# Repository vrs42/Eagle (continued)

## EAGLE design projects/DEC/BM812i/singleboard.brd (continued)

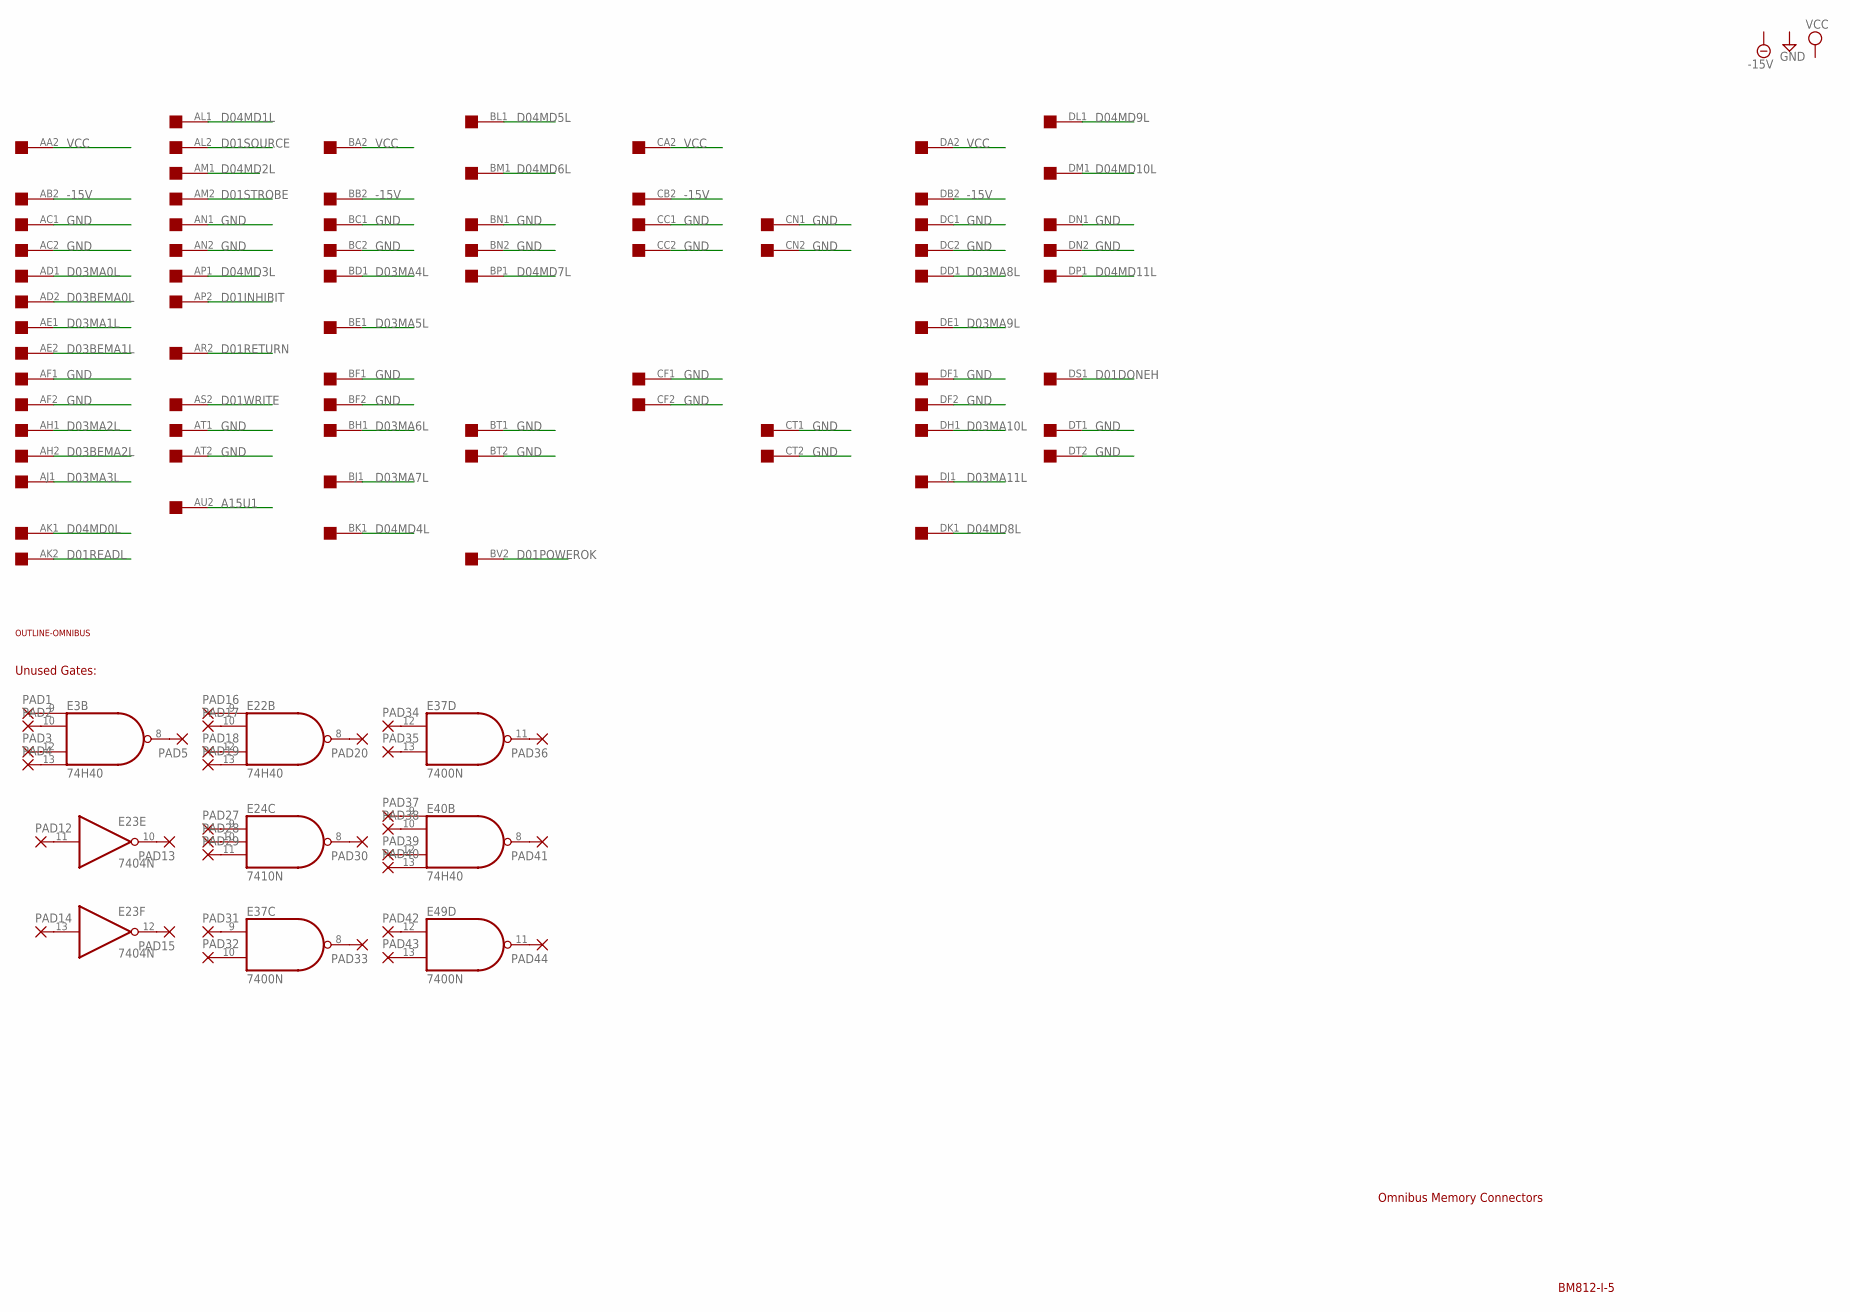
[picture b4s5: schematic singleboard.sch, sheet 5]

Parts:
E3, E22, E40: 74H40; DIL14
E23: 7404N; DIL14
E24: 7410N; DIL14
E37, E49: 7400N; DIL14
PAD1, PAD2, PAD3, PAD4, PAD5, PAD12, PAD13, PAD14, PAD15, PAD16, PAD17, PAD18, PAD19, PAD20, PAD27, PAD28, PAD29, PAD30, PAD31, PAD32, PAD33, PAD34, PAD35, PAD36, PAD37, PAD38, PAD39, PAD40, PAD41, PAD42, PAD43, PAD44: 1,6/0,8
U$1: QUAD; EDGE-CON8
U$2: OUTLINE-OMNIBUS; OMNIBUS

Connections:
-15V: U$1.AB2, U$1.BB2, U$1.CB2, U$1.DB2
A15U1: U$1.AU2; also elsewhere on the board
D01DONEH: U$1.DS1; also elsewhere on the board
D01INHIBIT: U$1.AP2; also elsewhere on the board
D01POWEROK: U$1.BV2; also elsewhere on the board
D01READL: U$1.AK2; also elsewhere on the board
D01RETURN: U$1.AR2; also elsewhere on the board
D01SOURCE: U$1.AL2; also elsewhere on the board
D01STROBE: U$1.AM2; also elsewhere on the board
D01WRITE: U$1.AS2; also elsewhere on the board
D03BEMA0L: U$1.AD2; also elsewhere on the board
D03BEMA1L: U$1.AE2; also elsewhere on the board
D03BEMA2L: U$1.AH2; also elsewhere on the board
D03MA0L: U$1.AD1; also elsewhere on the board
D03MA1L: U$1.AE1; also elsewhere on the board
D03MA2L: U$1.AH1; also elsewhere on the board
D03MA3L: U$1.AJ1; also elsewhere on the board
D03MA4L: U$1.BD1; also elsewhere on the board
D03MA5L: U$1.BE1; also elsewhere on the board
D03MA6L: U$1.BH1; also elsewhere on the board
D03MA7L: U$1.BJ1; also elsewhere on the board
D03MA8L: U$1.DD1; also elsewhere on the board
D03MA9L: U$1.DE1; also elsewhere on the board
D03MA10L: U$1.DH1; also elsewhere on the board
D03MA11L: U$1.DJ1; also elsewhere on the board
D04MD0L: U$1.AK1; also elsewhere on the board
D04MD1L: U$1.AL1; also elsewhere on the board
D04MD2L: U$1.AM1; also elsewhere on the board
D04MD3L: U$1.AP1; also elsewhere on the board
D04MD4L: U$1.BK1; also elsewhere on the board
D04MD5L: U$1.BL1; also elsewhere on the board
D04MD6L: U$1.BM1; also elsewhere on the board
D04MD7L: U$1.BP1; also elsewhere on the board
D04MD8L: U$1.DK1; also elsewhere on the board
D04MD9L: U$1.DL1; also elsewhere on the board
D04MD10L: U$1.DM1; also elsewhere on the board
D04MD11L: U$1.DP1; also elsewhere on the board
GND: E3.7 (GND), E22.7 (GND), E23.7 (GND), E24.7 (GND), E37.7 (GND), E40.7 (GND), E49.7 (GND), U$1.AC1, U$1.AC2, U$1.AF1, U$1.AF2, U$1.AN1, U$1.AN2, U$1.AT1, U$1.AT2, U$1.BC1, U$1.BC2, U$1.BF1, U$1.BF2, U$1.BN1, U$1.BN2, U$1.BT1, U$1.BT2, U$1.CC1, U$1.CC2, U$1.CF1, U$1.CF2, U$1.CN1, U$1.CN2, U$1.CT1, U$1.CT2, U$1.DC1, U$1.DC2, U$1.DF1, U$1.DF2, U$1.DN1, U$1.DN2, U$1.DT1, U$1.DT2; also elsewhere on the board
unnamed: E3.9 (I0), PAD1.1
unnamed: E3.10 (I1), PAD2.1
unnamed: E3.12 (I2), PAD3.1
unnamed: E3.13 (I3), PAD4.1
unnamed: E3.8 (O), PAD5.1
unnamed: E23.11 (I), PAD12.1
unnamed: E23.10 (O), PAD13.1
unnamed: E23.13 (I), PAD14.1
unnamed: E23.12 (O), PAD15.1
unnamed: E22.9 (I0), PAD16.1
unnamed: E22.10 (I1), PAD17.1
unnamed: E22.12 (I2), PAD18.1
unnamed: E22.13 (I3), PAD19.1
unnamed: E22.8 (O), PAD20.1
unnamed: E24.9 (I0), PAD27.1
unnamed: E24.10 (I1), PAD28.1
unnamed: E24.11 (I2), PAD29.1
unnamed: E24.8 (O), PAD30.1
unnamed: E37.9 (I0), PAD31.1
unnamed: E37.10 (I1), PAD32.1
unnamed: E37.8 (O), PAD33.1
unnamed: E37.12 (I0), PAD34.1
unnamed: E37.13 (I1), PAD35.1
unnamed: E37.11 (O), PAD36.1
unnamed: E40.9 (I0), PAD37.1
unnamed: E40.10 (I1), PAD38.1
unnamed: E40.12 (I2), PAD39.1
unnamed: E40.13 (I3), PAD40.1
unnamed: E40.8 (O), PAD41.1
unnamed: E49.12 (I0), PAD42.1
unnamed: E49.13 (I1), PAD43.1
unnamed: E49.11 (O), PAD44.1
VCC: E3.14 (VCC), E22.14 (VCC), E23.14 (VCC), E24.14 (VCC), E37.14 (VCC), E40.14 (VCC), E49.14 (VCC), U$1.AA2, U$1.BA2, U$1.CA2, U$1.DA2; also elsewhere on the board

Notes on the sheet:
Omnibus Memory Connectors
BM812-I-5
Unused Gates:

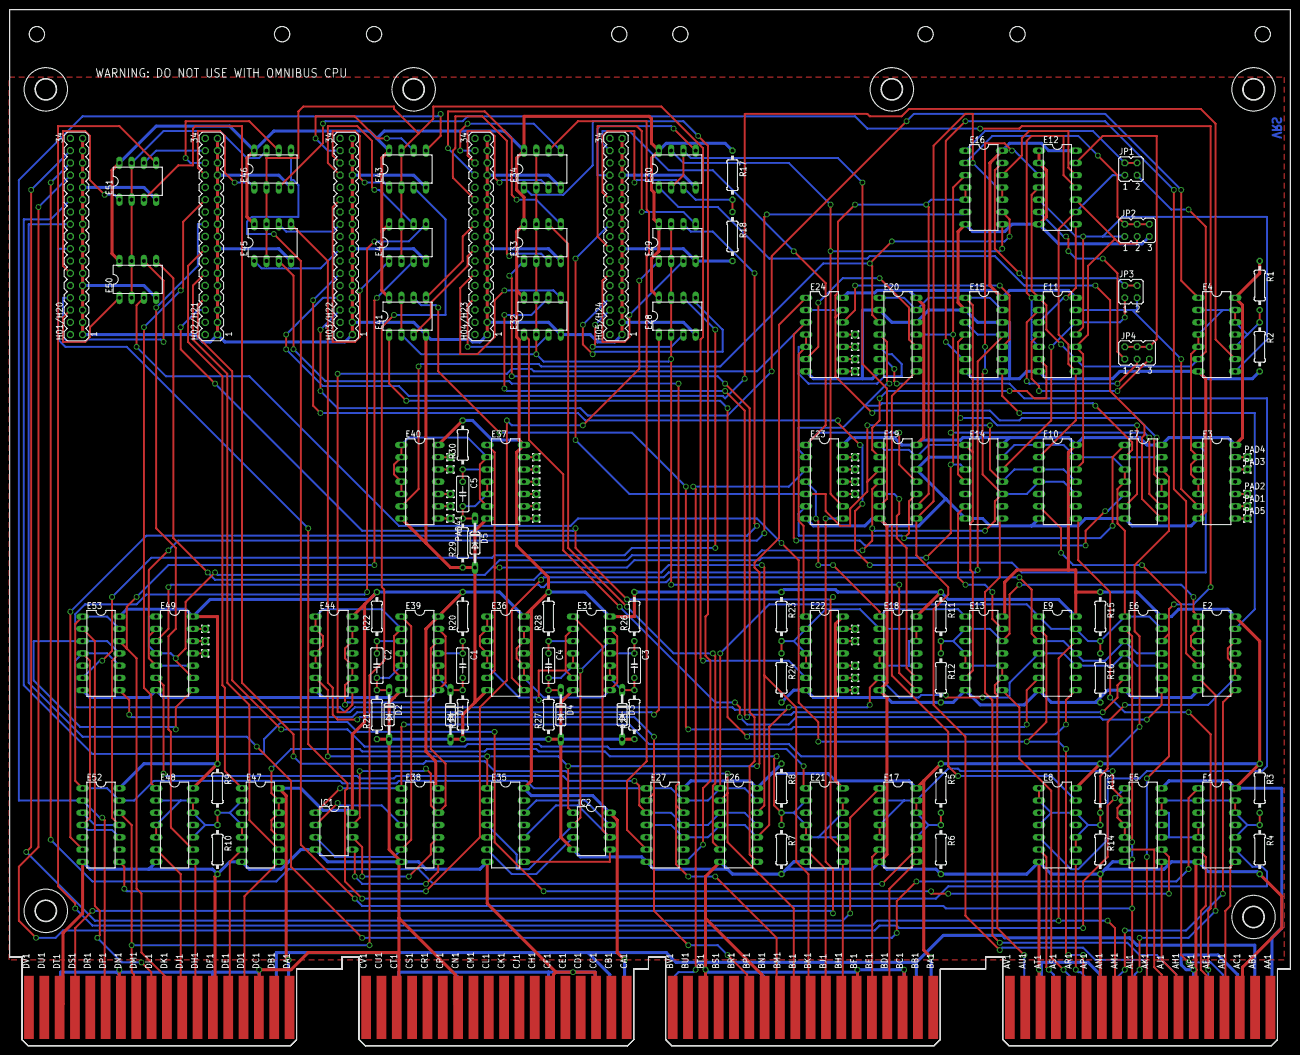
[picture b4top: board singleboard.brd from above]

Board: 2 copper layers, 265.3 x 214.6 mm, 143 parts (0 on the bottom side), 208 nets.

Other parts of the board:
U$20, U$66, U$67, U$82, U$83, U$86: 4,3

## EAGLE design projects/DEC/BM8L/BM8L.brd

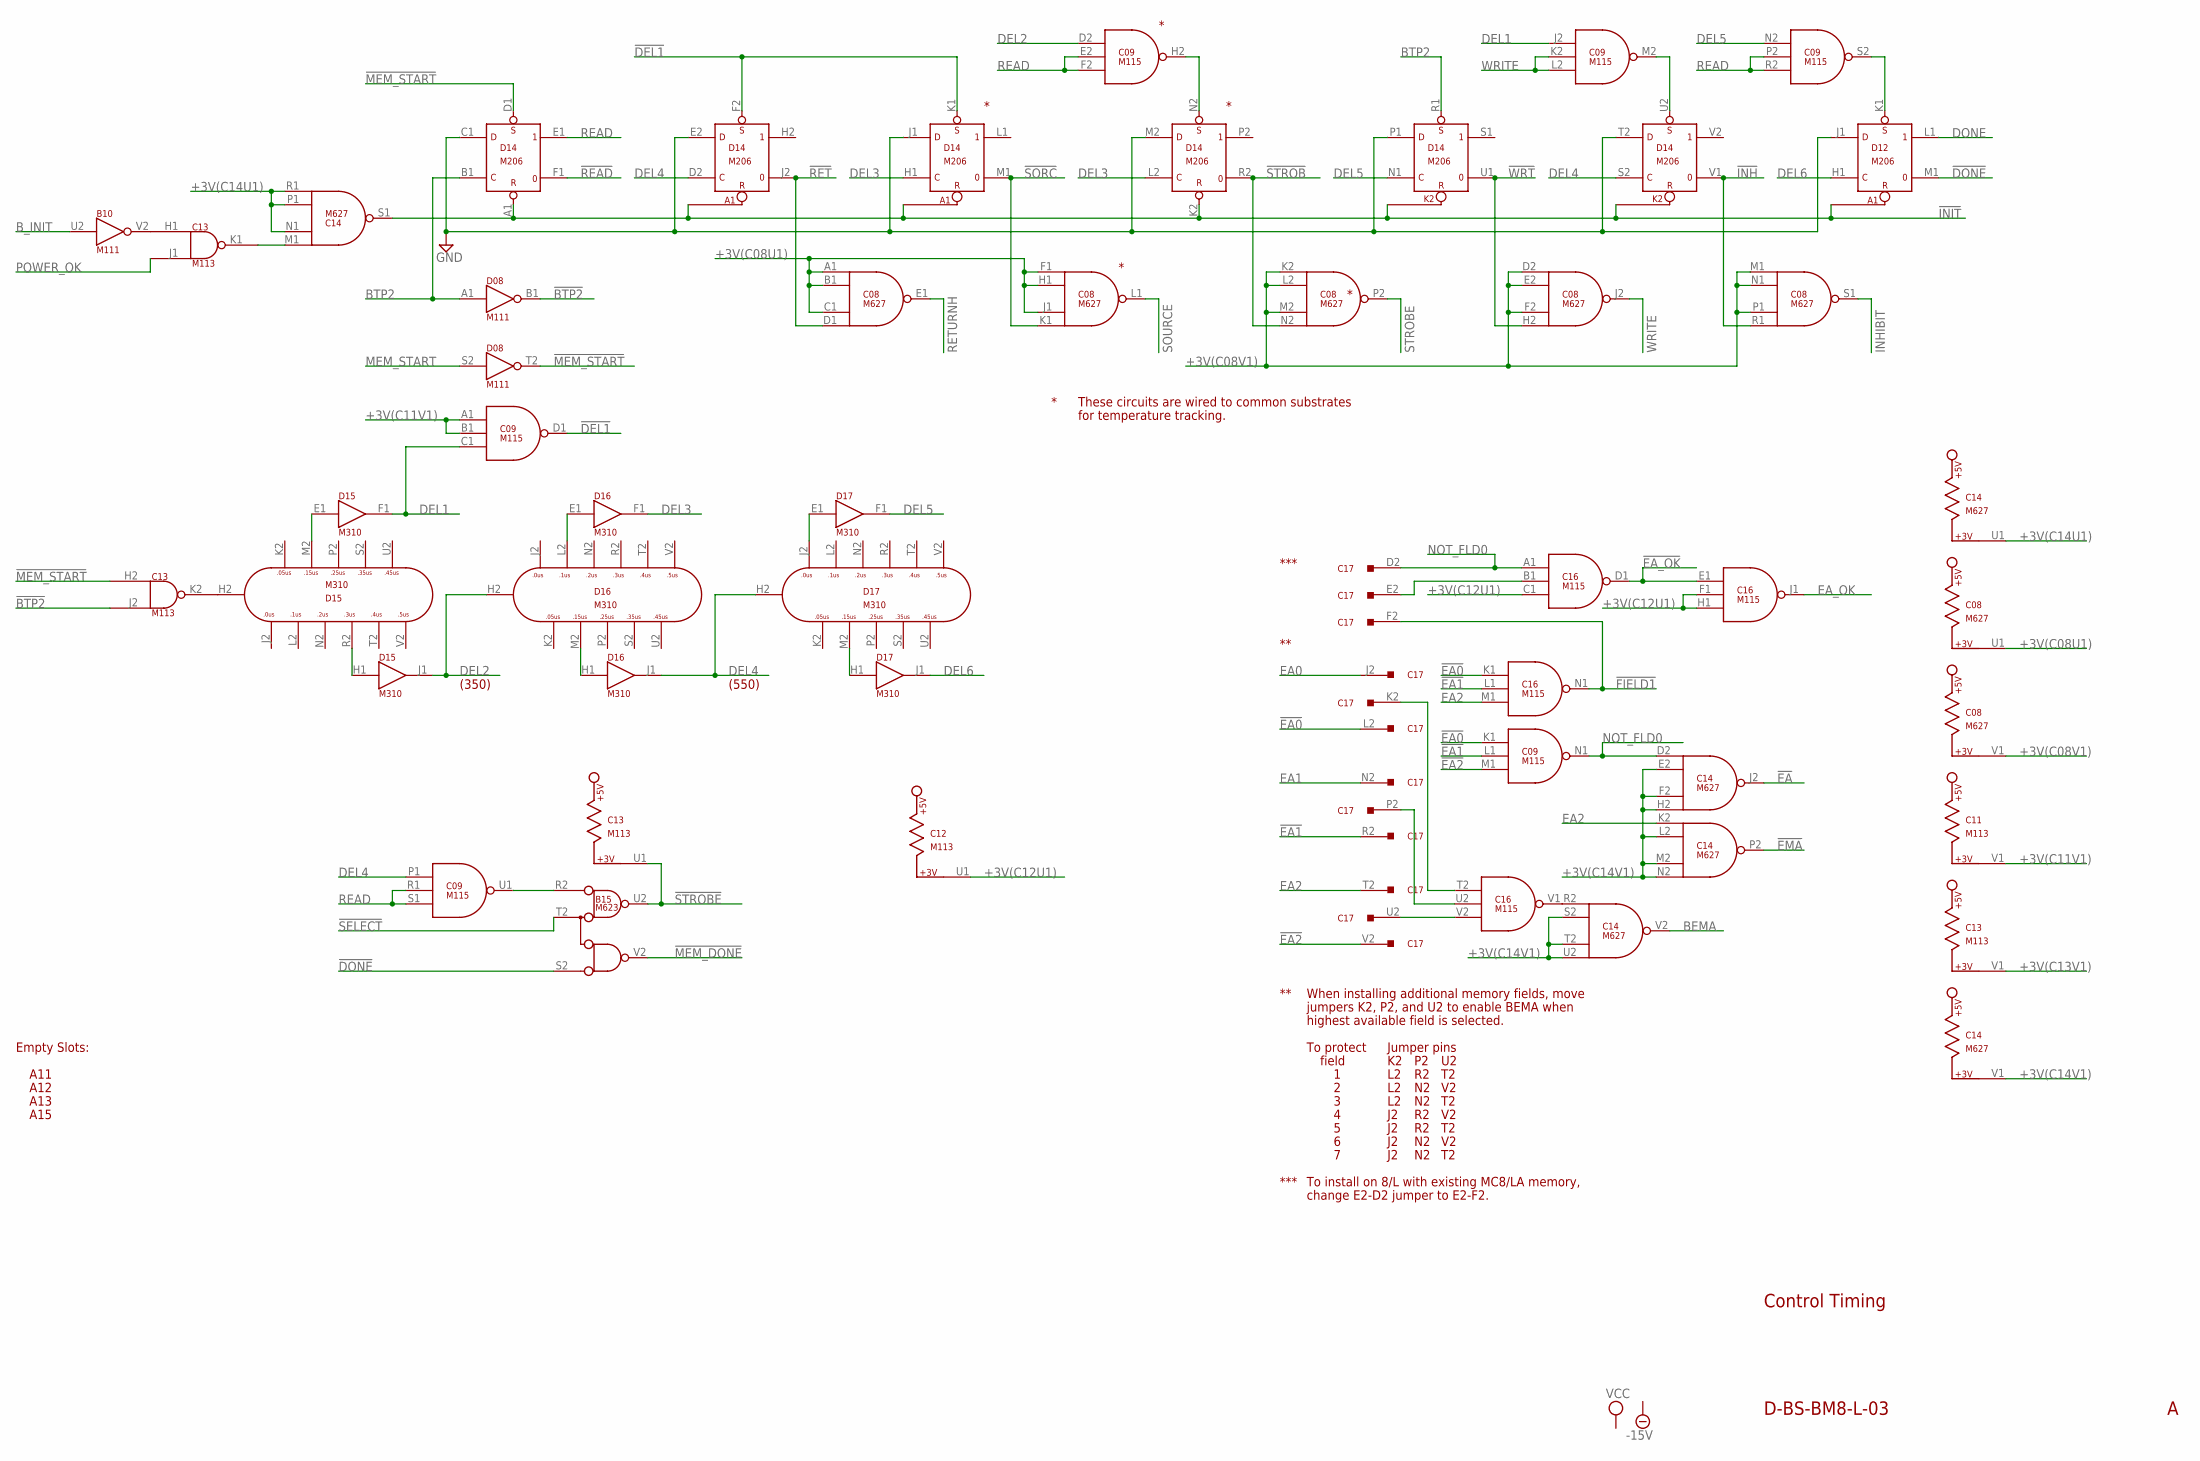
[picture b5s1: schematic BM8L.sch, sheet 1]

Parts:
A11, A12, A13, A15: EMPTY; H807
B10: M111; H807
B15: M623; H807
C08, C14: M627; H807
C09, C16: M115; H807
C11, C12, C13: M113; H807
C17: M990; H807
D08: M111; H807
D12, D14: M206; H807
D15, D16, D17: M310; H807

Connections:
!BTP2: C13.J2 (IN2), D08.B1 (OUT)
!DEL1: C09.D1 (OUT), D14.F2 (S), D14.K1 (S)
!DONE: B15.S2 (B), D12.M1 (0)
!EA: C14.J2 (OUT); also elsewhere on the board
!EA0: C09.K1 (IN1), C16.K1 (IN1), C17.L2; also elsewhere on the board
!EA1: C09.L1 (IN2), C16.L1 (IN2), C17.R2; also elsewhere on the board
!EA2: C09.M1 (IN3), C17.V2; also elsewhere on the board
!EA_OK: C16.D1 (OUT), C16.E1 (IN1)
!EMA: C14.P2 (OUT); also elsewhere on the board
!FIELD1: C16.N1 (OUT), C17.F2; also elsewhere on the board
!INH: C08.R1 (IN4), D14.V1 (0)
!INIT: C14.S1 (OUT), D14.A1 (R), D14.K2 (R); also elsewhere on the board
!MEM_DONE: B15.V2 (E); also elsewhere on the board
!MEM_START: C13.H2 (IN1), D08.T2 (OUT), D14.D1 (S)
!READ: D14.F1 (0); also elsewhere on the board
!RET: C08.D1 (IN4), D14.J2 (0)
!SELECT: B15.T2 (C); also elsewhere on the board
!SORC: C08.K1 (IN4), D14.M1 (0)
!STROB: C08.N2 (IN4), D14.R2 (0)
!STROBE: B15.U2 (D), C13.U1; also elsewhere on the board
!WRT: C08.H2 (IN4), D14.U1 (0)
+3V(C08U1): C08.A1 (IN1), C08.B1 (IN2), C08.C1 (IN3), C08.F1 (IN1), C08.H1 (IN2), C08.J1 (IN3), C08.U1; also elsewhere on the board
+3V(C08V1): C08.D2 (IN1), C08.E2 (IN2), C08.F2 (IN3), C08.K2 (IN1), C08.L2 (IN2), C08.M1 (IN1), C08.M2 (IN3), C08.N1 (IN2), C08.P1 (IN3), C08.V1
+3V(C11V1): C09.A1 (IN1), C09.B1 (IN2), C11.V1; also elsewhere on the board
+3V(C12U1): C12.U1, C16.C1 (IN3), C16.F1 (IN2), C16.H1 (IN3)
+3V(C13V1): C13.V1; also elsewhere on the board
+3V(C14U1): C14.N1 (IN2), C14.P1 (IN3), C14.R1 (IN4), C14.U1; also elsewhere on the board
+3V(C14V1): C14.E2 (IN2), C14.F2 (IN3), C14.H2 (IN4), C14.L2 (IN2), C14.M2 (IN3), C14.N2 (IN4), C14.S2 (IN2), C14.T2 (IN3), C14.U2 (IN4), C14.V1
-15V: A11.B2 (-15V), A12.B2 (-15V), A13.B2 (-15V), A15.B2 (-15V); also elsewhere on the board
BEMA: C14.V2 (OUT); also elsewhere on the board
BTP2: D08.A1 (IN), D14.B1 (C), D14.R1 (S); also elsewhere on the board
B_INIT: B10.U2 (IN); also elsewhere on the board
DEL1: C09.C1 (IN3), C09.J2 (IN1), D15.F1 (OUT)
DEL2: C09.D2 (IN1), D15.J1 (OUT), D16.H2; also elsewhere on the board
DEL3: D14.H1 (C), D14.L2 (C), D16.F1 (OUT); also elsewhere on the board
DEL4: C09.P1 (IN1), D14.D2 (C), D14.S2 (C), D16.J1 (OUT), D17.H2; also elsewhere on the board
DEL5: C09.N2 (IN1), D14.N1 (C), D17.F1 (OUT)
DEL6: D12.H1 (C), D17.J1 (OUT)
DONE: D12.L1 (1); also elsewhere on the board
EA0: C17.J2; also elsewhere on the board
EA1: C17.N2; also elsewhere on the board
EA2: C14.K2 (IN1), C16.M1 (IN3), C17.T2; also elsewhere on the board
EA_OK: C16.J1 (OUT); also elsewhere on the board
GND: A11.C2 (GND), A12.C2 (GND), A13.C2 (GND), A15.C2 (GND), B10.C2 (GND), B10.T1 (GND), B15.C2 (GND), B15.T1 (GND), B15.U1 (GND), B15.V1 (GND), C08.C2 (GND), C08.T1 (GND), C09.C2 (GND), C09.T1 (GND), C11.C2 (GND), C11.T1 (GND), C12.C2 (GND), C12.T1 (GND), C13.C2 (GND), C13.T1 (GND), C14.C2 (GND), C14.T1 (GND), C16.C2 (GND), C16.T1 (GND), D08.C2 (GND), D08.T1 (GND), D12.C2 (GND), D12.J1 (D), D12.T1 (GND), D14.C1 (D), D14.C2 (GND), D14.E2 (D), D14.J1 (D), D14.M2 (D), D14.P1 (D), D14.T1 (GND), D14.T2 (D), D15.C2 (GND), D15.T1 (GND), D16.C2 (GND), D16.T1 (GND), D17.C2 (GND), D17.T1 (GND); also elsewhere on the board
INHIBIT: C08.S1 (OUT); also elsewhere on the board
MEM_START: D08.S2 (IN); also elsewhere on the board
unnamed: B10.V2 (OUT), C13.H1 (IN1)
unnamed: C13.K1 (OUT), C14.M1 (IN1)
unnamed: B15.R2 (A), C09.U1 (OUT)
unnamed: C09.M2 (OUT), D14.U2 (S)
unnamed: C13.K2 (OUT), D15.H2
unnamed: D15.H1 (IN), D15.R2
unnamed: D15.E1 (IN), D15.M2
unnamed: D16.E1 (IN), D16.L2
unnamed: D16.H1 (IN), D16.M2
unnamed: D17.E1 (IN), D17.J2
unnamed: D17.H1 (IN), D17.M2
unnamed: C16.V2 (IN3), C17.U2
unnamed: C16.U2 (IN2), C17.P2
unnamed: C16.T2 (IN1), C17.K2
unnamed: C14.R2 (IN1), C16.V1 (OUT)
unnamed: C16.B1 (IN2), C17.E2
unnamed: C09.H2 (OUT), D14.N2 (S)
unnamed: C09.S2 (OUT), D12.K1 (S)
NOT_FLD0: C09.N1 (OUT), C14.D2 (IN1), C16.A1 (IN1), C17.D2
POWER_OK: C13.J1 (IN2); also elsewhere on the board
READ: C09.E2 (IN2), C09.F2 (IN3), C09.P2 (IN2), C09.R1 (IN2), C09.R2 (IN3), C09.S1 (IN3), D14.E1 (1); also elsewhere on the board
RETURNH: C08.E1 (OUT); also elsewhere on the board
SOURCE: C08.L1 (OUT); also elsewhere on the board
STROBE: C08.P2 (OUT); also elsewhere on the board
VCC: A11.A2 (VCC), A12.A2 (VCC), A13.A2 (VCC), A15.A2 (VCC), B10.A2 (VCC), B15.A2 (VCC), C08.A2 (VCC), C09.A2 (VCC), C11.A2 (VCC), C12.A2 (VCC), C13.A2 (VCC), C14.A2 (VCC), C16.A2 (VCC), D08.A2 (VCC), D12.A2 (VCC), D14.A2 (VCC), D15.A2 (VCC), D16.A2 (VCC), D17.A2 (VCC); also elsewhere on the board
WRITE: C08.J2 (OUT), C09.K2 (IN2), C09.L2 (IN3); also elsewhere on the board

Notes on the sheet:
D-BS-BM8-L-03
Control Timing
When installing additional memory fields, move
jumpers K2, P2, and U2 to enable BEMA when
highest available field is selected.
To protect
field
Jumper pins
To install on 8/L with existing MC8/LA memory,
change E2-D2 jumper to E2-F2.
***
(350)
These circuits are wired to common substrates
for temperature tracking.
(550)
Empty Slots:

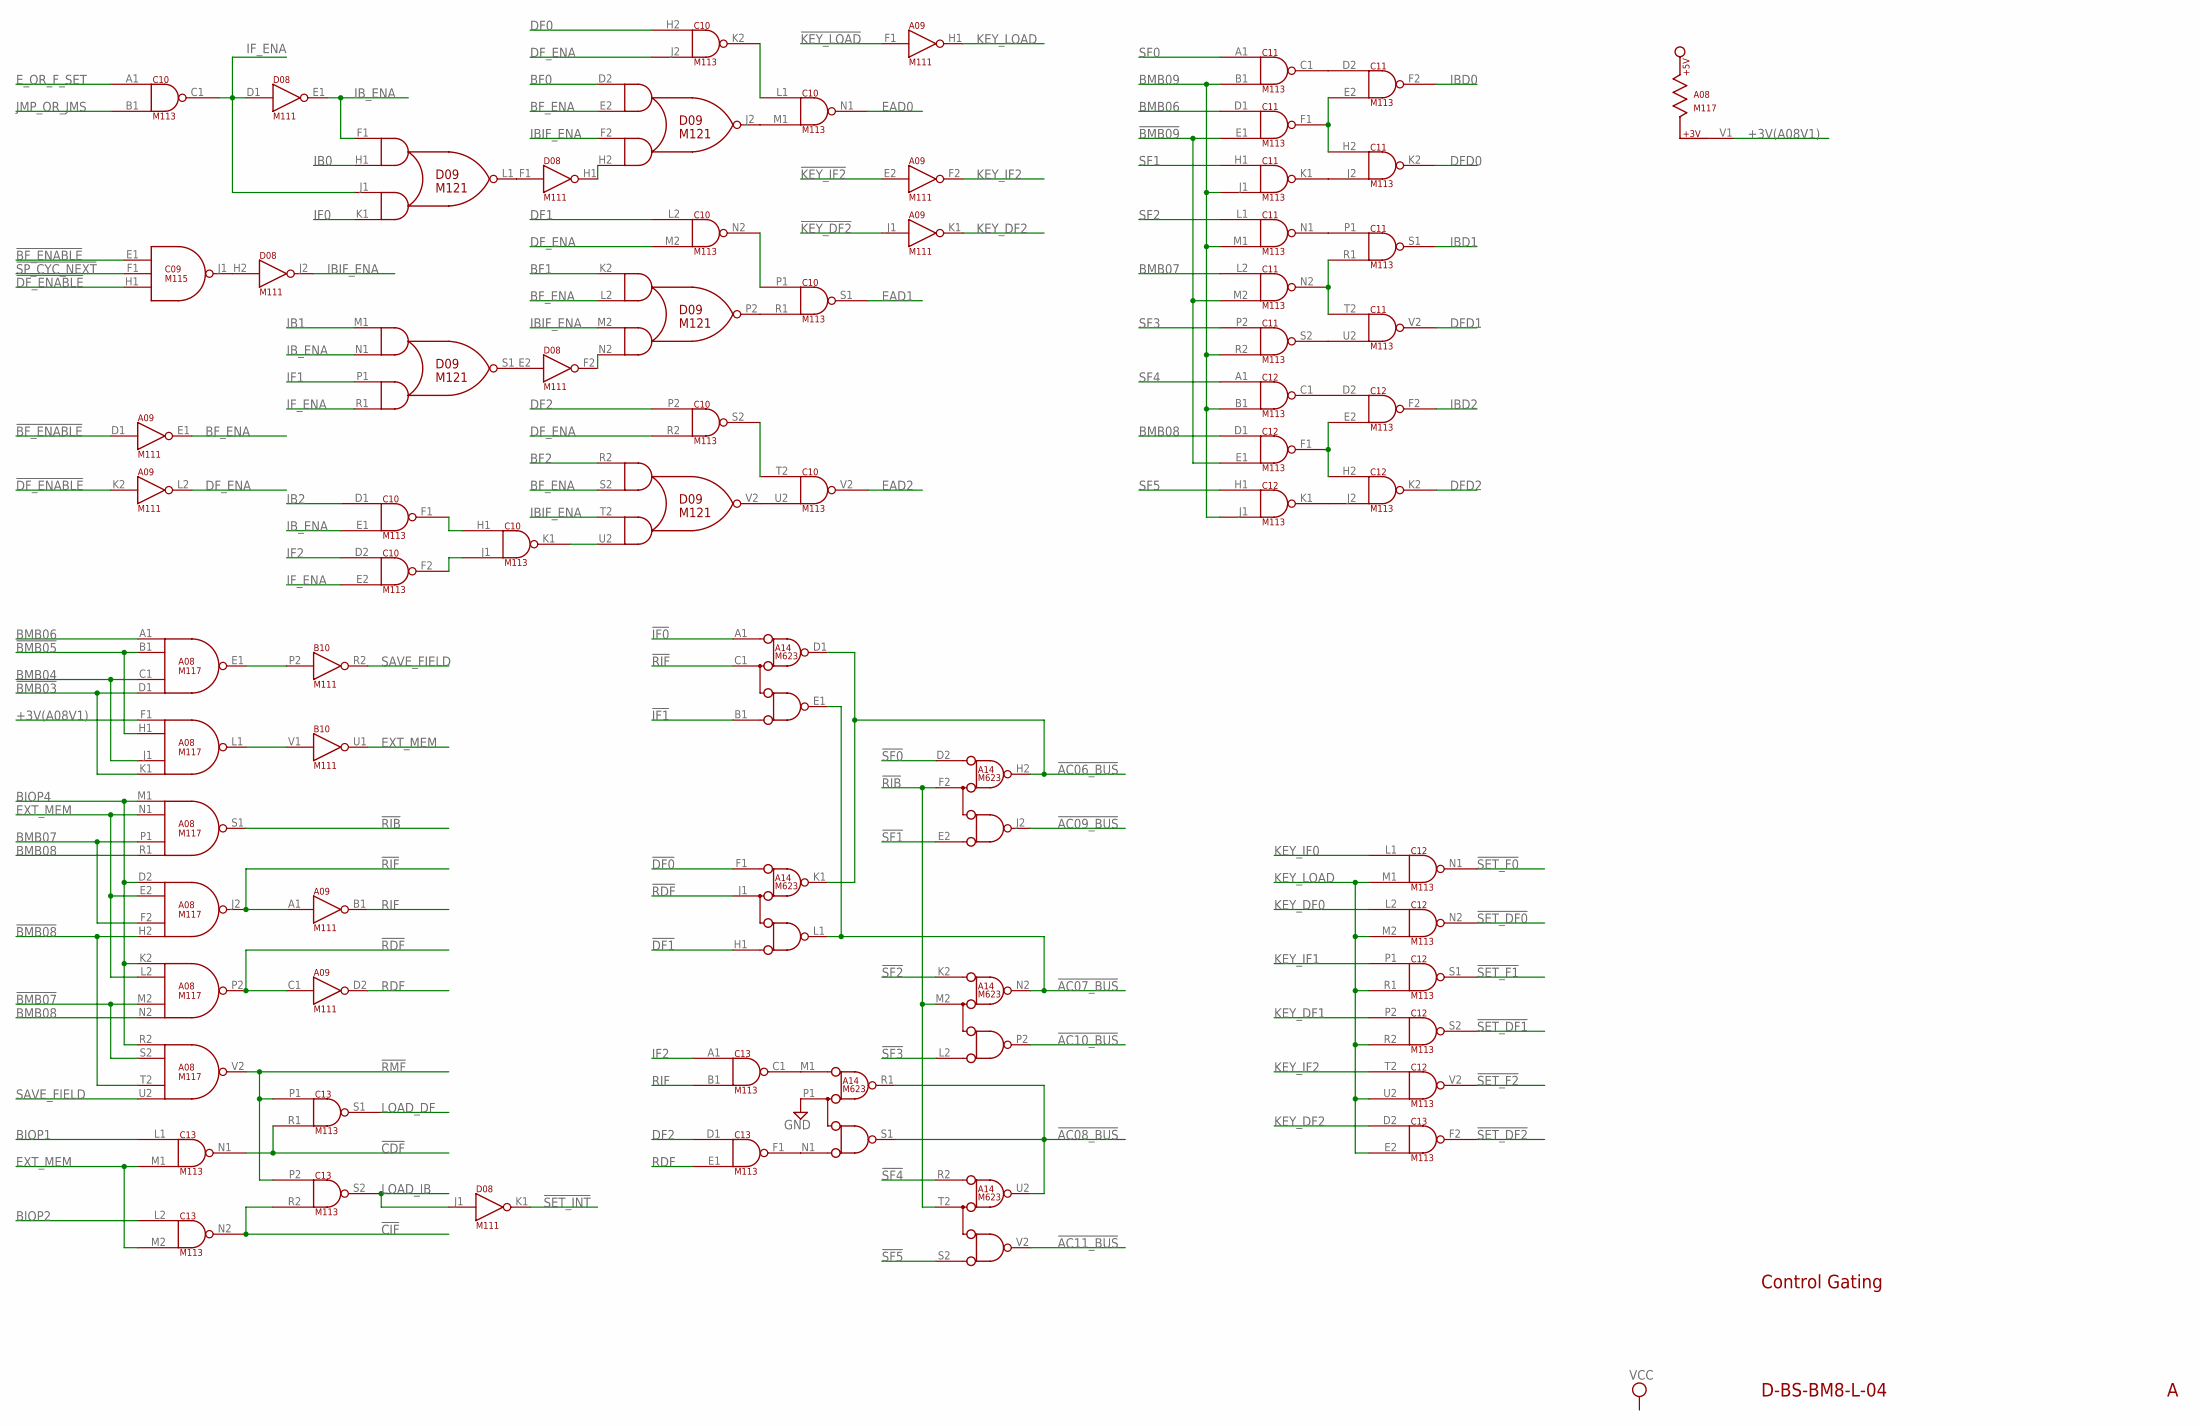
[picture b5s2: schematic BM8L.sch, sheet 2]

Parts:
A08: M117; H807
A09: M111; H807
A14: M623; H807
B10: M111; H807
C09: M115; H807
C10, C11, C12, C13: M113; H807
D08: M111; H807
D09: M121; H807

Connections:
!AC06_BUS: A14.D1 (D), A14.H2 (D), A14.K1 (D); also elsewhere on the board
!AC07_BUS: A14.E1 (E), A14.L1 (E), A14.N2 (D); also elsewhere on the board
!AC08_BUS: A14.R1 (D), A14.S1 (E), A14.U2 (D); also elsewhere on the board
!AC09_BUS: A14.J2 (E); also elsewhere on the board
!AC10_BUS: A14.P2 (E); also elsewhere on the board
!AC11_BUS: A14.V2 (E); also elsewhere on the board
!BF_ENABLE: A09.D1 (IN), C09.E1 (IN1); also elsewhere on the board
!BMB03: A08.D1 (IN4), A08.K1 (IN4); also elsewhere on the board
!BMB05: A08.B1 (IN2), A08.H1 (IN2); also elsewhere on the board
!BMB07: A08.M2 (IN3), A08.S2 (IN2); also elsewhere on the board
!BMB08: A08.H2 (IN4), A08.T2 (IN3); also elsewhere on the board
!BMB09: C11.E1 (IN2), C11.M2 (IN2), C12.E1 (IN2); also elsewhere on the board
!CDF: C13.N1 (OUT), C13.R1 (IN2)
!CIF: C13.N2 (OUT), C13.R2 (IN2)
!DF0: A14.F1 (A); also elsewhere on the board
!DF1: A14.H1 (B); also elsewhere on the board
!DF_ENABLE: A09.K2 (IN), C09.H1 (IN3); also elsewhere on the board
!IF0: A14.A1 (A); also elsewhere on the board
!IF1: A14.B1 (B); also elsewhere on the board
!KEY_DF2: A09.J1 (IN); also elsewhere on the board
!KEY_IF2: A09.E2 (IN); also elsewhere on the board
!KEY_LOAD: A09.F1 (IN); also elsewhere on the board
!RDF: A08.P2 (OUT), A09.C1 (IN), A14.J1 (C)
!RIB: A08.S1 (OUT), A14.F2 (C), A14.M2 (C), A14.T2 (C)
!RIF: A08.J2 (OUT), A09.A1 (IN), A14.C1 (C)
!RMF: A08.V2 (OUT), C13.P1 (IN1), C13.P2 (IN1)
!SET_DF0: C12.N2 (OUT); also elsewhere on the board
!SET_DF1: C12.S2 (OUT); also elsewhere on the board
!SET_DF2: C13.F2 (OUT); also elsewhere on the board
!SET_F0: C12.N1 (OUT); also elsewhere on the board
!SET_F1: C12.S1 (OUT); also elsewhere on the board
!SET_F2: C12.V2 (OUT); also elsewhere on the board
!SET_INT: D08.K1 (OUT); also elsewhere on the board
!SF0: A14.D2 (A); also elsewhere on the board
!SF1: A14.E2 (B); also elsewhere on the board
!SF2: A14.K2 (A); also elsewhere on the board
!SF3: A14.L2 (B); also elsewhere on the board
!SF4: A14.R2 (A); also elsewhere on the board
!SF5: A14.S2 (B); also elsewhere on the board
!SP_CYC_NEXT: C09.F1 (IN2); also elsewhere on the board
+3V(A08V1): A08.F1 (IN1), A08.V1; also elsewhere on the board
BF0: D09.D2 (IN1A); also elsewhere on the board
BF1: D09.K2 (IN1A); also elsewhere on the board
BF2: D09.R2 (IN1A); also elsewhere on the board
BF_ENA: A09.E1 (OUT), D09.E2 (IN1B), D09.L2 (IN1B), D09.S2 (IN1B)
BIOP1: C13.L1 (IN1); also elsewhere on the board
BIOP2: C13.L2 (IN1); also elsewhere on the board
BIOP4: A08.D2 (IN1), A08.K2 (IN1), A08.M1 (IN1), A08.R2 (IN1); also elsewhere on the board
BMB04: A08.C1 (IN3), A08.J1 (IN3); also elsewhere on the board
BMB06: A08.A1 (IN1), C11.D1 (IN1); also elsewhere on the board
BMB07: A08.F2 (IN3), A08.P1 (IN3), C11.L2 (IN1); also elsewhere on the board
BMB08: A08.N2 (IN4), A08.R1 (IN4), C12.D1 (IN1); also elsewhere on the board
BMB09: C11.B1 (IN2), C11.J1 (IN2), C11.M1 (IN2), C11.R2 (IN2), C12.B1 (IN2), C12.J1 (IN2); also elsewhere on the board
DF0: C10.H2 (IN1); also elsewhere on the board
DF1: C10.L2 (IN1); also elsewhere on the board
DF2: C10.P2 (IN1), C13.D1 (IN1); also elsewhere on the board
DFD0: C11.K2 (OUT); also elsewhere on the board
DFD1: C11.V2 (OUT); also elsewhere on the board
DFD2: C12.K2 (OUT); also elsewhere on the board
DF_ENA: A09.L2 (OUT), C10.J2 (IN2), C10.M2 (IN2), C10.R2 (IN2)
EAD0: C10.N1 (OUT); also elsewhere on the board
EAD1: C10.S1 (OUT); also elsewhere on the board
EAD2: C10.V2 (OUT); also elsewhere on the board
EXT_MEM: A08.E2 (IN2), A08.L2 (IN2), A08.N1 (IN2), B10.U1 (OUT), C13.M1 (IN2), C13.M2 (IN2)
E_OR_F_SET: C10.A1 (IN1); also elsewhere on the board
GND: A08.C2 (GND), A08.T1 (GND), A09.C2 (GND), A09.T1 (GND), A14.C2 (GND), A14.P1 (C), A14.T1 (GND), A14.U1 (GND), A14.V1 (GND), B10.C2 (GND), B10.T1 (GND), C09.C2 (GND), C09.T1 (GND), C10.C2 (GND), C10.T1 (GND), C11.C2 (GND), C11.T1 (GND), C12.C2 (GND), C12.T1 (GND), C13.C2 (GND), C13.T1 (GND), D08.C2 (GND), D08.T1 (GND), D09.C2 (GND), D09.T1 (GND); also elsewhere on the board
IB0: D09.H1 (IN1B); also elsewhere on the board
IB1: D09.M1 (IN1A); also elsewhere on the board
IB2: C10.D1 (IN1); also elsewhere on the board
IBD0: C11.F2 (OUT); also elsewhere on the board
IBD1: C11.S1 (OUT); also elsewhere on the board
IBD2: C12.F2 (OUT); also elsewhere on the board
IBIF_ENA: D08.J2 (OUT), D09.F2 (IN2A), D09.M2 (IN2A), D09.T2 (IN2A)
IB_ENA: C10.E1 (IN2), D08.E1 (OUT), D09.F1 (IN1A), D09.N1 (IN1B)
IF0: D09.K1 (IN2B); also elsewhere on the board
IF1: D09.P1 (IN2A); also elsewhere on the board
IF2: C10.D2 (IN1), C13.A1 (IN1); also elsewhere on the board
IF_ENA: C10.C1 (OUT), C10.E2 (IN2), D08.D1 (IN), D09.J1 (IN2A), D09.R1 (IN2B)
JMP_OR_JMS: C10.B1 (IN2); also elsewhere on the board
KEY_DF0: C12.L2 (IN1); also elsewhere on the board
KEY_DF1: C12.P2 (IN1); also elsewhere on the board
KEY_DF2: A09.K1 (OUT), C13.D2 (IN1)
KEY_IF0: C12.L1 (IN1); also elsewhere on the board
KEY_IF1: C12.P1 (IN1); also elsewhere on the board
KEY_IF2: A09.F2 (OUT), C12.T2 (IN1)
KEY_LOAD: A09.H1 (OUT), C12.M1 (IN2), C12.M2 (IN2), C12.R1 (IN2), C12.R2 (IN2), C12.U2 (IN2), C13.E2 (IN2)
LOAD_DF: C13.S1 (OUT); also elsewhere on the board
LOAD_IB: C13.S2 (OUT), D08.J1 (IN); also elsewhere on the board
unnamed: D08.F1 (IN), D09.L1 (OUT)
unnamed: D08.H1 (OUT), D09.H2 (IN2B)
unnamed: C10.K2 (OUT), C10.L1 (IN1)
unnamed: C10.M1 (IN2), D09.J2 (OUT)
unnamed: D08.E2 (IN), D09.S1 (OUT)
unnamed: D08.F2 (OUT), D09.N2 (IN2B)
unnamed: C10.R1 (IN2), D09.P2 (OUT)
unnamed: C10.N2 (OUT), C10.P1 (IN1)
unnamed: C10.K1 (OUT), D09.U2 (IN2B)
unnamed: C10.F1 (OUT), C10.H1 (IN1)
unnamed: C10.F2 (OUT), C10.J1 (IN2)
unnamed: C09.J1 (OUT), D08.H2 (IN)
unnamed: C11.E2 (IN2), C11.F1 (OUT), C11.H2 (IN1)
unnamed: C11.N1 (OUT), C11.P1 (IN1)
unnamed: C10.U2 (IN2), D09.V2 (OUT)
unnamed: C10.S2 (OUT), C10.T2 (IN1)
unnamed: C11.J2 (IN2), C11.K1 (OUT)
unnamed: C11.C1 (OUT), C11.D2 (IN1)
unnamed: C11.S2 (OUT), C11.U2 (IN2)
unnamed: C11.N2 (OUT), C11.R1 (IN2), C11.T2 (IN1)
unnamed: C12.E2 (IN2), C12.F1 (OUT), C12.H2 (IN1)
unnamed: C12.C1 (OUT), C12.D2 (IN1)
unnamed: C12.J2 (IN2), C12.K1 (OUT)
unnamed: A14.M1 (A), C13.C1 (OUT)
unnamed: A08.E1 (OUT), B10.P2 (IN)
unnamed: A08.L1 (OUT), B10.V1 (IN)
unnamed: A14.N1 (B), C13.F1 (OUT)
RDF: A09.D2 (OUT), C13.E1 (IN2)
RIF: A09.B1 (OUT), C13.B1 (IN2)
SAVE_FIELD: A08.U2 (IN4), B10.R2 (OUT)
SF0: C11.A1 (IN1); also elsewhere on the board
SF1: C11.H1 (IN1); also elsewhere on the board
SF2: C11.L1 (IN1); also elsewhere on the board
SF3: C11.P2 (IN1); also elsewhere on the board
SF4: C12.A1 (IN1); also elsewhere on the board
SF5: C12.H1 (IN1); also elsewhere on the board
VCC: A08.A2 (VCC), A09.A2 (VCC), A14.A2 (VCC), B10.A2 (VCC), C09.A2 (VCC), C10.A2 (VCC), C11.A2 (VCC), C12.A2 (VCC), C13.A2 (VCC), D08.A2 (VCC), D09.A2 (VCC); also elsewhere on the board

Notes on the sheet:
D-BS-BM8-L-04
Control Gating
